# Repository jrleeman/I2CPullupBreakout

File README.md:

# I2C Pullup Breakout

## Purpose

Prototyping aid that allows selectable pull-up and series resistors for the I2C
bus. To use, just insert the module into your circuit/breadboard and select the
appropriate series/pull up resistor values with the solder  jumpers. Bridging
the jumpers is very easy and switching usually just requires a swipe with the
soldering iron.

## Purchasing

The I2C Pullup Breakout is available through Leeman Geophysical by emailing
[John R. Leeman](http://www.johnrleeman.com) at <kd5wxb@gmail.com>.

## Project Information

This repository includes all design information, CAD files, PDF CAD output,
gerbers, etc.

Additional resources for this project include:

- [Bill of Materials](BoM.md) (BoM)

## License

This product is licenced under the CERN Open Hardware License 1.2. The [full
license](cern_ohl_v_1_2.txt) is included in this repository.

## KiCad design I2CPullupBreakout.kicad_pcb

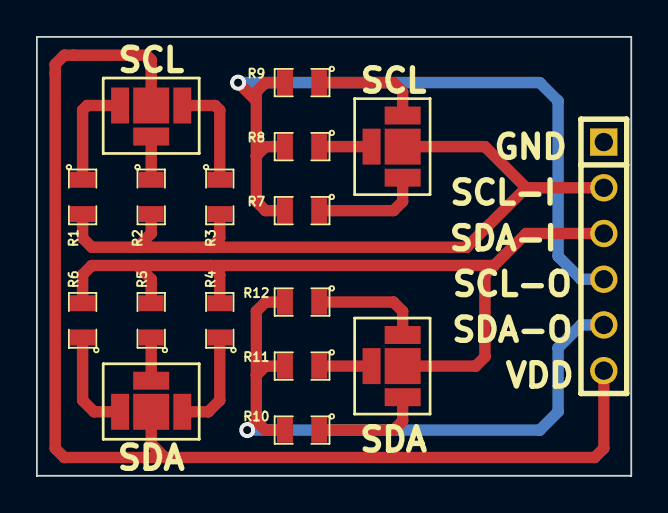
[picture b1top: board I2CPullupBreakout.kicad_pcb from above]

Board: 2 copper layers, 33.0 x 24.4 mm, 17 parts (0 on the bottom side), 17 nets.

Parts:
J1, J2, J3, J4: SPDT_JUMPER; Solder_SPTT
P1: CONN_6; PIN_ARRAY-6X1
R1, R6, R7, R10: 0; SM0805
R2, R5, R8, R11: 470; SM0805
R3, R4, R9, R12: 10K; SM0805

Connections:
+3.3V: J1.1, J2.1, P1.6
/SCL_IN: J3.1, P1.2, R1.2, R2.2, R3.2
/SCL_OUT: P1.4, R7.2, R8.2, R9.2
/SDA_IN: J4.1, P1.3, R4.2, R5.2, R6.2
/SDA_OUT: P1.5, R10.2, R11.2, R12.2
unnamed: J4.4, R12.1
unnamed: J4.2, R10.1
unnamed: J4.3, R11.1
unnamed: J3.2, R7.1
unnamed: J3.3, R8.1
unnamed: J3.4, R9.1
unnamed: J2.2, R6.1
unnamed: J2.3, R5.1
unnamed: J2.4, R4.1
unnamed: J1.2, R3.1
unnamed: J1.4, R1.1
unnamed: J1.3, R2.1

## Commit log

2014-12-07 Initial commit of Rev.A
2014-12-07 Update readme and associated info
2014-12-07 Add schematic PDF and rev number.
2014-12-07 Add use instructions
